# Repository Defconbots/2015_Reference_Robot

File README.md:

2015_Reference_Robot
====================

The laser used for the contest is the **50 mW** version of this laser: http://www.civillaser.com/532nm-5mw50mw-ttl-modulation-green-laser-module-dot-16mmx70mm-p-130.html

You'll need a controller to run the robot. The source for the controller can be found in the /hw folder.

Software to run the reference robot is in the /sw/TowerDefenderMkII folder.

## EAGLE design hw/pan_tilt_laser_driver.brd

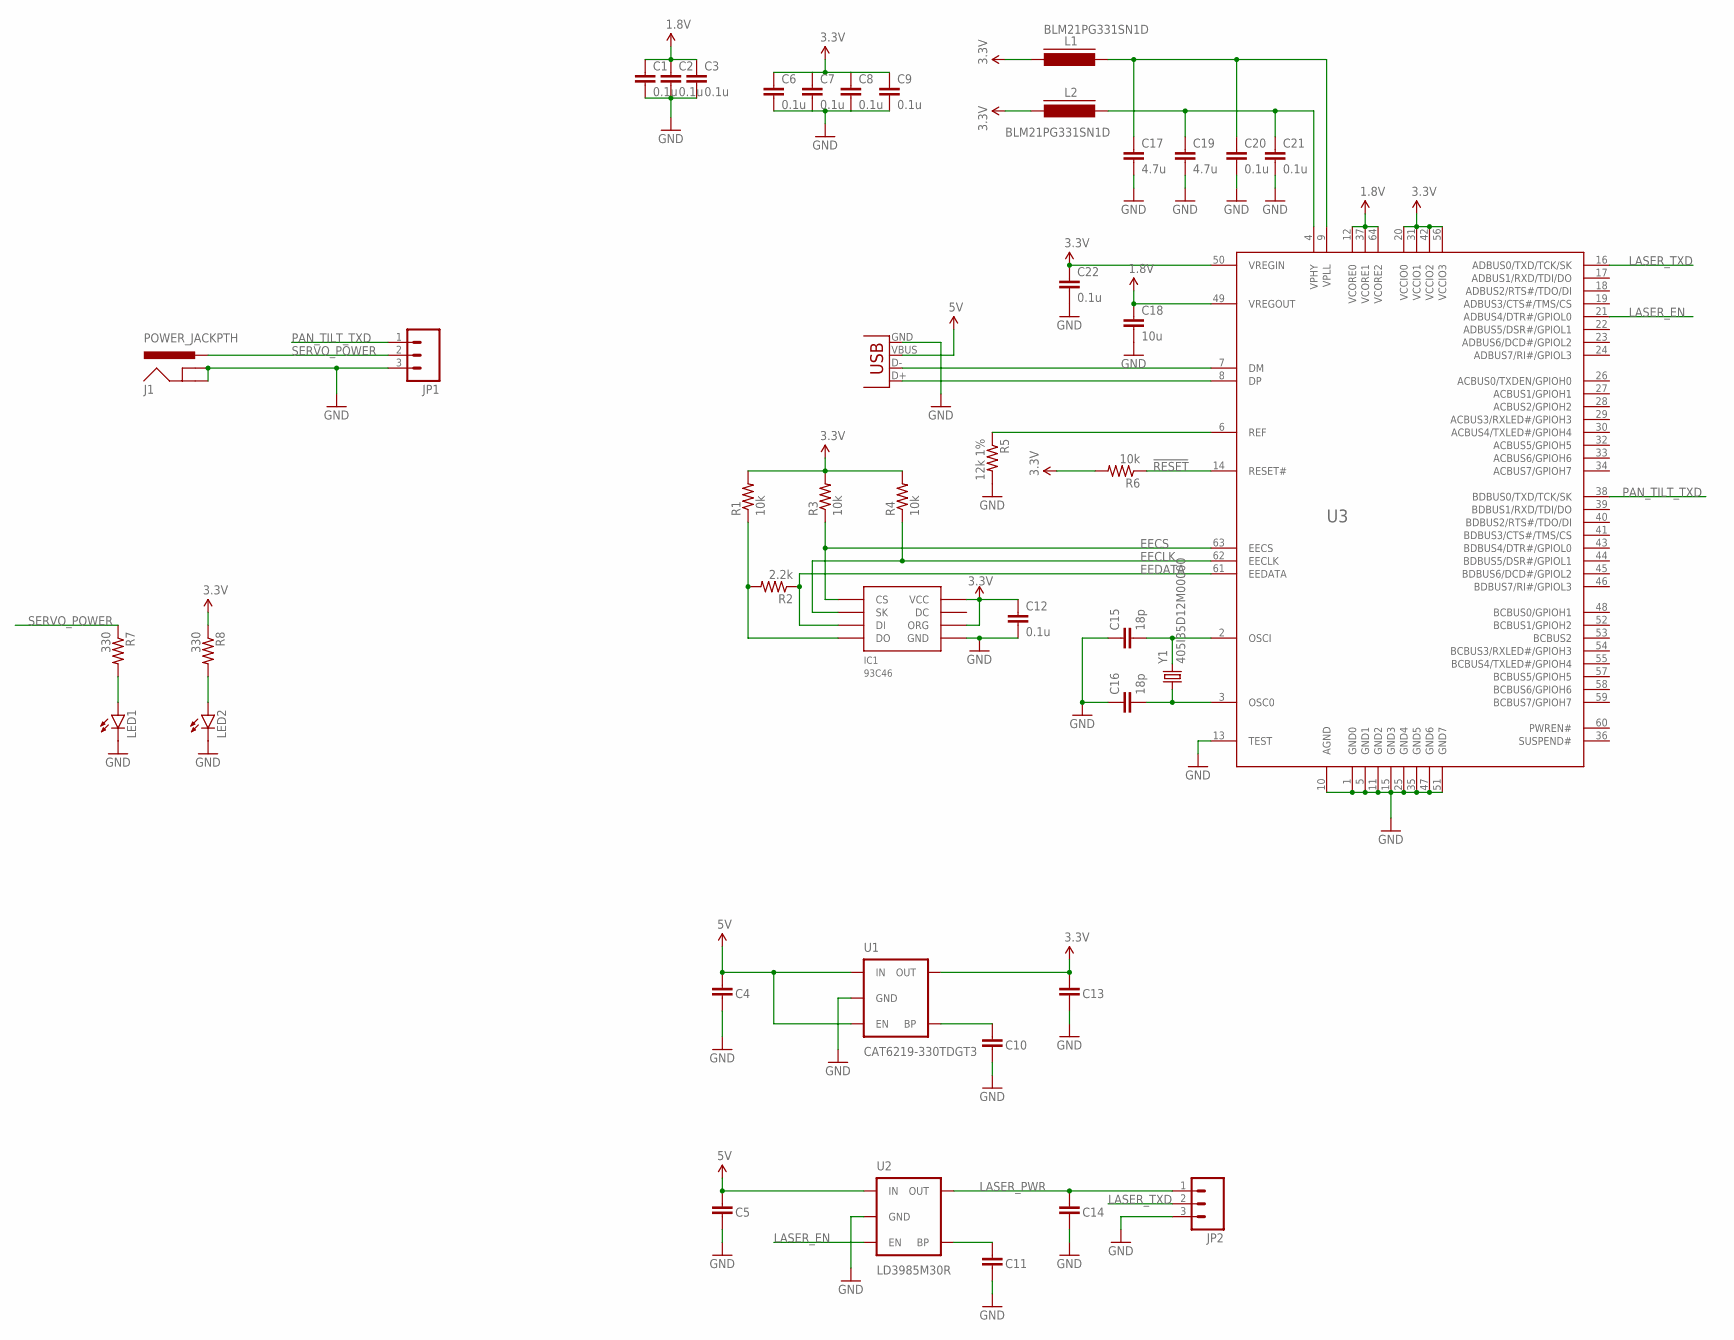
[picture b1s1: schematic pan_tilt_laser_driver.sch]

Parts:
C1, C2, C3, C6, C7, C8, C9, C12, C20, C21, C22: 0.1u; C0603K
C4, C5, C13, C14: 10u; 0603-CAP
C10, C11: 0.01u; 0603-CAP
C15, C16: 18p; C0603K
C17, C19: 4.7u; C0603K
C18: 10u; C0603K
IC1: 93C46; SOIC8
J1: POWER_JACKPTH; POWER_JACK_PTH
JP1: M0322-03-5035; 22-03-5035
JP2: 651-5442251; SCREWTERMINAL-3.5MM-3
L1, L2: BLM21PG331SN1D; FB805
LED1, LED2: LED1206; LED-1206
R1, R3, R4, R6: 10k; R0603
R2: 2.2k; R0603
R5: 12k 1%; R0603
R7, R8: 330; R0603
U1: CAT6219-330TDGT3; SOT23-5
U2: LD3985M30R; SOT23-5
U3: FT2232H; LQFP64
X1: 538-47346-0001; USB-MICROB
Y1: 405I35D12M00000; CRYSTAL-SMD-5X3

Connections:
1.8V: C1.1, C2.1, C3.1, C18.1, U3.12 (VCORE0), U3.37 (VCORE1), U3.49 (VREGOUT), U3.64 (VCORE2)
3.3V: C6.1, C7.1, C8.1, C9.1, C12.1, C13.1, C22.1, IC1.6 (ORG), IC1.8 (VCC), L1.2, L2.2, R1.2, R3.2, R4.2, R6.2, R8.1, U1.5 (OUT), U3.20 (VCCIO0), U3.31 (VCCIO1), U3.42 (VCCIO2), U3.50 (VREGIN), U3.56 (VCCIO3)
5V: C4.1, C5.1, U1.1 (IN), U1.3 (EN), U2.1 (IN), X1.VBUS
!RESET: R6.1, U3.14 (RESET#)
EECLK: IC1.2 (SK), R4.1, U3.62 (EECLK)
EECS: IC1.1 (CS), R3.1, U3.63 (EECS)
EEDATA: IC1.3 (DI), R2.1, U3.61 (EEDATA)
GND: C1.2, C2.2, C3.2, C4.2, C5.2, C6.2, C7.2, C8.2, C9.2, C10.2, C11.2, C12.2, C13.2, C14.2, C15.1, C16.1, C17.2, C18.2, C19.2, C20.2, C21.2, C22.2, IC1.5 (GND), J1.GND, J1.GNDBREAK, JP1.3, JP2.3, LED1.C, LED2.C, R5.2, U1.2 (GND), U2.2 (GND), U3.1 (GND0), U3.5 (GND1), U3.10 (AGND), U3.11 (GND2), U3.13 (TEST), U3.15 (GND3), U3.25 (GND4), U3.35 (GND5), U3.47 (GND6), U3.51 (GND7), X1.GND
LASER_EN: U2.3 (EN), U3.21 (ADBUS4/DTR#/GPIOL0)
LASER_PWR: C14.1, JP2.1, U2.5 (OUT)
LASER_TXD: JP2.2, U3.16 (ADBUS0/TXD/TCK/SK)
unnamed: C11.1, U2.4 (BP)
unnamed: LED1.A, R7.2
unnamed: U3.7 (DM), X1.D-
unnamed: R5.1, U3.6 (REF)
unnamed: U3.8 (DP), X1.D+
unnamed: C17.1, C20.1, L1.1, U3.9 (VPLL)
unnamed: C15.2, U3.2 (OSCI), Y1.3 (2)
unnamed: C10.1, U1.4 (BP)
unnamed: C19.1, C21.1, L2.1, U3.4 (VPHY)
unnamed: C16.2, U3.3 (OSC0), Y1.1
unnamed: LED2.A, R8.2
unnamed: IC1.4 (DO), R1.1, R2.2
PAN_TILT_TXD: JP1.1, U3.38 (BDBUS0/TXD/TCK/SK)
SERVO_POWER: J1.PWR, JP1.2, R7.1

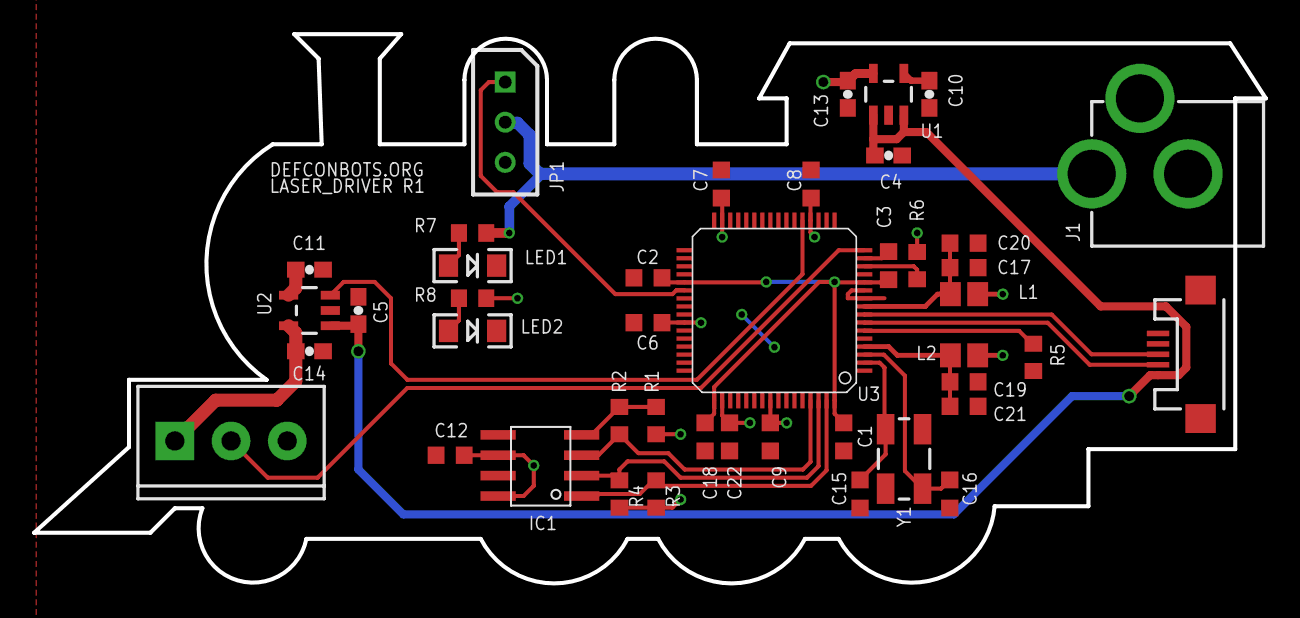
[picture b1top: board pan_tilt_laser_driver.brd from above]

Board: 2 copper layers, 76.7 x 34.2 mm, 43 parts (0 on the bottom side), 25 nets.

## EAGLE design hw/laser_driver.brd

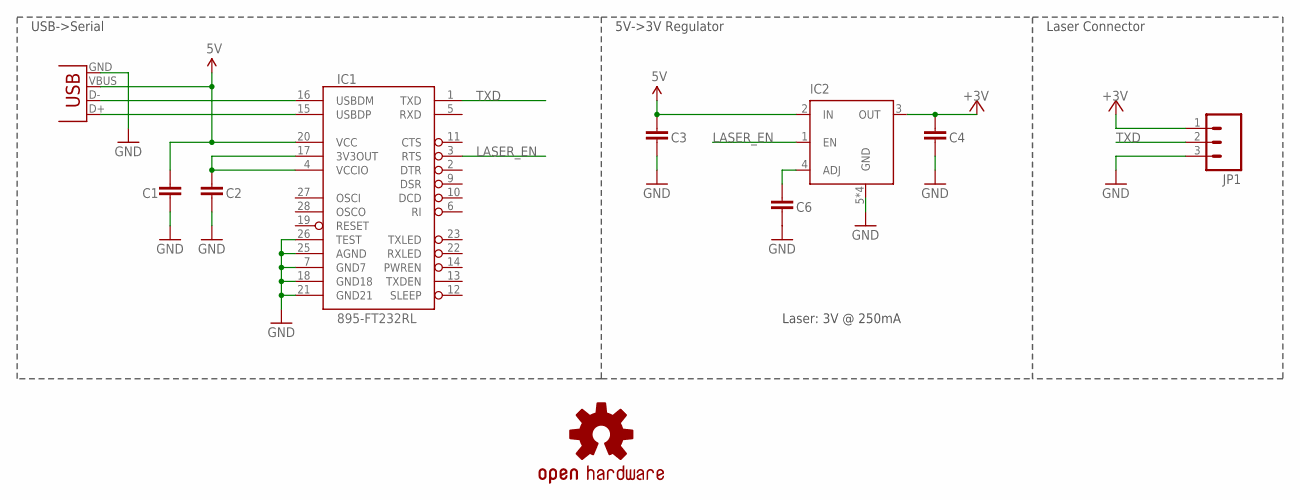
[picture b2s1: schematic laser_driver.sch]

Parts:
C1, C2, C3, C4: C1608X5R1C106M080AB; 0603-CAP
C6: VJ0603A471KXQPW1BC; 0603-CAP
IC1: 895-FT232RL; SSOP28DB
IC2: 998-MIC5219-3.0YMM; MSOP08
JP1: 651-5442251; SCREWTERMINAL-3.5MM-3
LOGO1: OSHW-LOGOS; OSHW-LOGO-S
X1: 798-ZX62RD-AB-5P8; USB-MICROB

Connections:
3.3V: C2.1, IC1.4 (VCCIO), IC1.17 (3V3OUT)
5V: C1.1, C3.1, IC1.20 (VCC), IC2.2 (IN), X1.VBUS
+3V: C4.1, IC2.3 (OUT), JP1.1
GND: C1.2, C2.2, C3.2, C4.2, C6.2, IC1.7 (GND7), IC1.18 (GND18), IC1.21 (GND21), IC1.25 (AGND), IC1.26 (TEST), IC2.5 (GND), IC2.6 (GND), IC2.7 (GND), IC2.8 (GND), JP1.3, X1.GND
LASER_EN: IC1.3 (RTS), IC2.1 (EN)
unnamed: C6.1, IC2.4 (ADJ)
TXD: IC1.1 (TXD), JP1.2
USB_D+: IC1.15 (USBDP), X1.D+
USB_D-: IC1.16 (USBDM), X1.D-

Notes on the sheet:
USB->Serial
5V->3V Regulator
Laser Connector
Laser: 3V @ 250mA

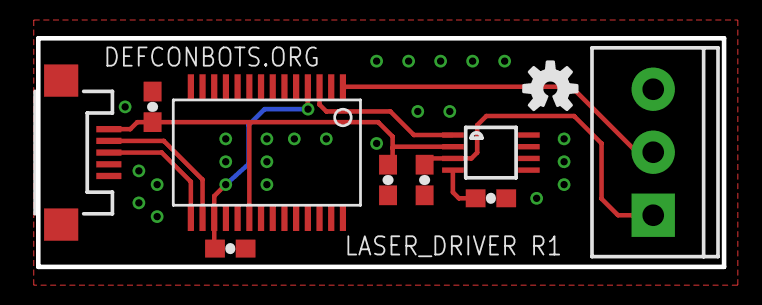
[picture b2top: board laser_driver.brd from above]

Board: 2 copper layers, 38.1 x 12.7 mm, 10 parts (0 on the bottom side), 9 nets.

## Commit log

2014-12-05 First pass at laser driver using ft232
2014-12-05 Change connector to terminal block
2014-12-09 Add license
2014-12-09 Cleanup for fab. Add bom and gerbers.
2014-12-09 Fix noise cap for the regulator
2015-01-02 Fix part numbers for regulator and usb plug. Fix disconnectoed ground pin (4) which was a really stupid mistake...
2015-03-31 Rough schematic with FT2232H
2015-04-02 Outline replaced, in progress
2015-04-02 Preliminary placement complete.
2015-04-03 Round Signal Routing
2015-04-03 Rough Signal Routing
2015-04-05 Finished initial routing.
2015-05-10 Final version of the ref hw.
2015-05-10 Maker faire demo app. Thrown together at the last minute..
2015-05-12 Fix the threading
2015-05-15 initial relative control of camera
2015-06-09 Fix part number for USB micro connector (was wrong direction part -- upside down).
2015-06-09 Servo connector was backwards. Fixed in schematic and layout.
2015-07-05 TowerDefender MkII
    Initial Commit, TowerDefender updated to use 50mW laser

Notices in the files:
parts and their libraries:
SparkFun-Passives: Licensing: CC v3.0 Share-Alike You are welcome to use this library for commercial purposes.
SparkFun-Aesthetics: Licensing: Creative Commons ShareAlike 4.0 International - https://creativecommons.org/licenses/by-sa/4.0
